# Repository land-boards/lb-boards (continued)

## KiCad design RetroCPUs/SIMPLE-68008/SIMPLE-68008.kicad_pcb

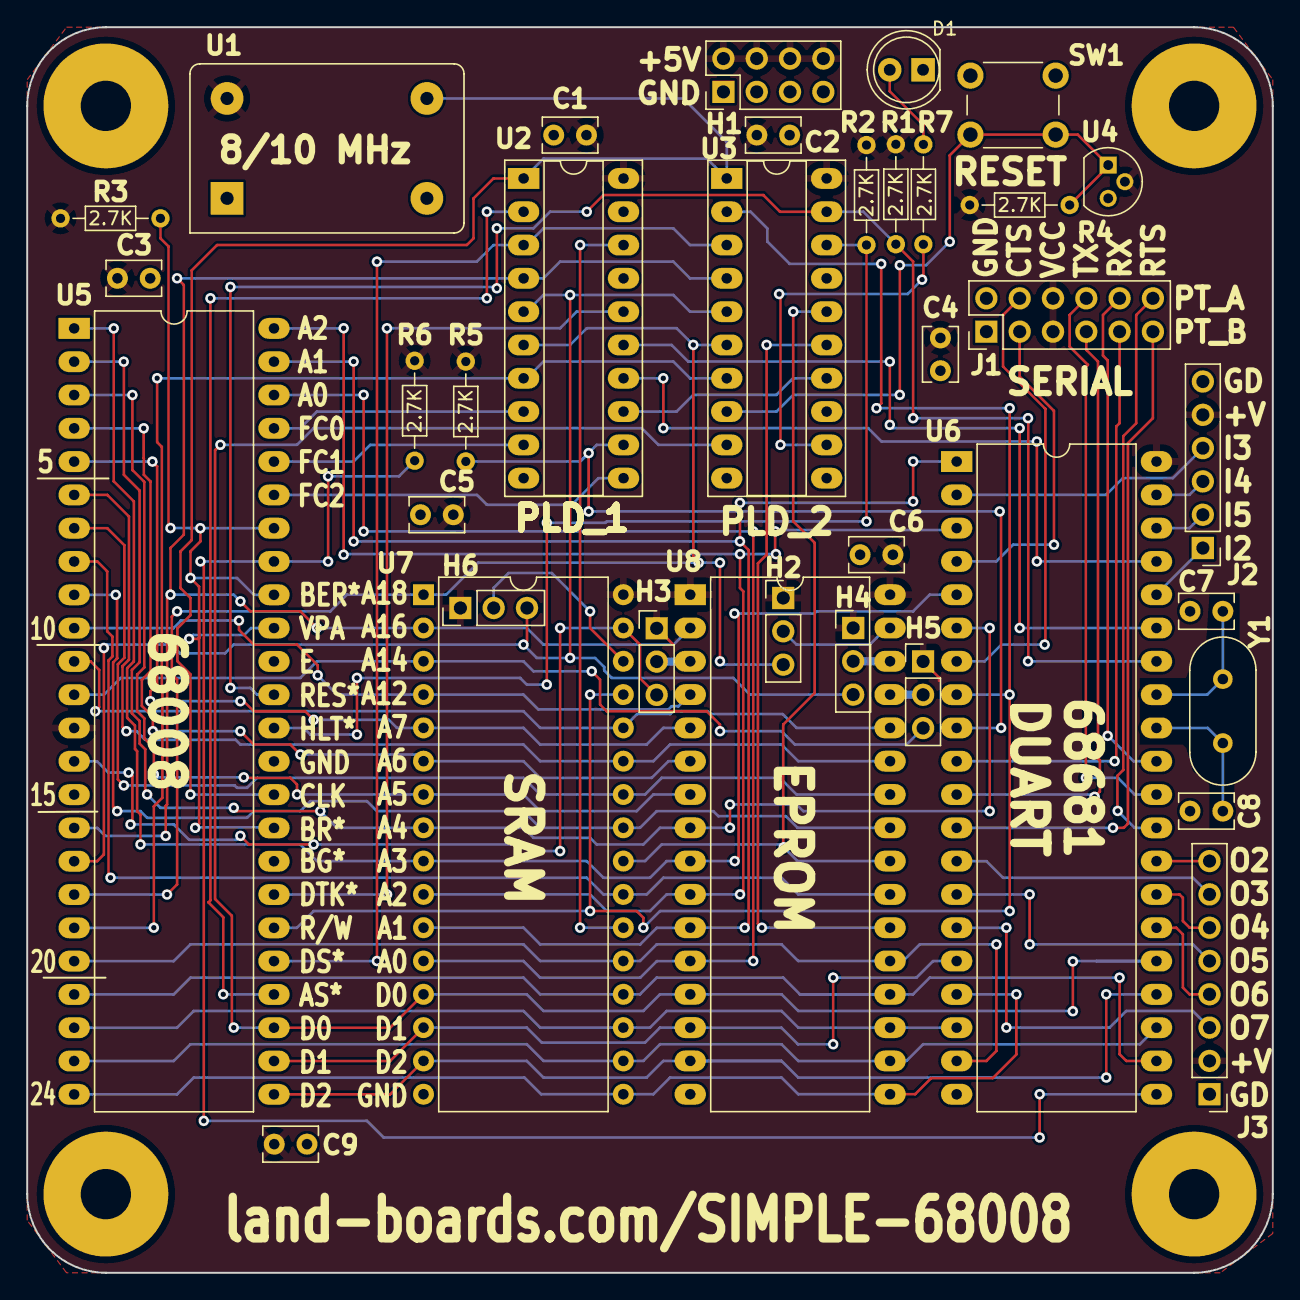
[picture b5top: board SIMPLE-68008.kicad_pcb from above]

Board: 2 copper layers, 95.0 x 95.0 mm, 41 parts (0 on the bottom side), 77 nets.

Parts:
C1, C2, C3, C4, C5, C6, C9: 0.1uF; C_Rect_L4.0mm_W2.5mm_P2.50mm
C7: 0-5pf; C_Rect_L4.0mm_W2.5mm_P2.50mm
C8: 10-15pF; C_Rect_L4.0mm_W2.5mm_P2.50mm
D1: LED_Filled; LED_D5.0mm
H1: HEADER, STRT, 2X4; PinHeader_2x04_P2.54mm_Vertical
H2, H3, H4, H5, H6: JUMPER (1X3); PinHeader_1x03_P2.54mm_Vertical
J1: Conn_02x06_Odd_Even; PinHeader_2x06_P2.54mm_Vertical
J2: Conn_01x06; PinHeader_1x06_P2.54mm_Vertical
J3: Conn_01x08; PinHeader_1x08_P2.54mm_Vertical
MTG1, MTG2, MTG3, MTG4: MTG_HOLE; MTG-6-32
R1, R2, R3, R4, R5, R6, R7: 2.7K; R_Axial_DIN0204_L3.6mm_D1.6mm_P7.62mm_Horizontal
SW1: PUSHBUTTON, 6MM; SW_PUSH_6mm_H8.5mm
TEST: COUPON; TEST_BLK-REAR
U1: 10 MHz; Oscillator_DIP-14_LargePads
U2, U3: GAL16V8; DIP-20_W7.62mm_Socket_LongPads
U4: DS1813-5 (OPT); TO-92
U5: MC68008D-10; DIP-48_W15.24mm_LongPads
U6: 68681; DIP-40_W15.24mm_LongPads
U7: AS6C4008-55PCN; DIP-32_W15.24mm
U8: 27C040; DIP-32_W15.24mm_LongPads
Y1: 3.6864 MHz; Crystal_HC49-U_Vertical

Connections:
/CPUA0: U5.46 (A0), U7.12 (A0), U8.12 (A0)
/CPUA1: U5.47 (A1), U6.1 (RS1), U7.11 (A1), U8.11 (A1)
/CPUA2: U5.48 (A2), U6.3 (RS2), U7.10 (A2), U8.10 (A2)
/CPUA3: U5.1 (A3), U6.5 (RS3), U7.9 (A3), U8.9 (A3)
/CPUA4: U5.2 (A4), U6.6 (RS4), U7.8 (A4), U8.8 (A4)
/CPUA5: U5.3 (A5), U7.7 (A5), U8.7 (A5)
/CPUA6: U5.4 (A6), U7.6 (A6), U8.6 (A6)
/CPUA7: U5.5 (A7), U7.5 (A7), U8.5 (A7)
/CPUA8: U5.6 (A8), U7.27 (A8), U8.27 (A8)
/CPUA9: U5.7 (A9), U7.26 (A9), U8.26 (A9)
/CPUA10: U5.8 (A10), U7.23 (A10), U8.23 (A10)
/CPUA11: U5.9 (A11), U7.25 (A11), U8.25 (A11)
/CPUA12: U5.10 (A12), U7.4 (A12), U8.4 (A12)
/CPUA13: U5.11 (A13), U7.28 (A13), U8.28 (A13)
/CPUA14: H5.3, U5.12 (A14), U7.3 (A14)
/CPUA15: H3.3, U5.14 (A15), U7.31 (A15)
/CPUA16: U2.4 (I4), U3.4 (I4), U5.16 (A16), U7.2 (A16), U8.2 (A16)
/CPUA17: H4.3, H6.3, U2.5 (I5), U3.5 (I5), U5.17 (A17)
/CPUA18: H2.3, U2.6 (I6), U3.6 (I6), U5.18 (A18), U7.1 (A18)
/CPUA19: U2.7 (I7), U3.7 (I7), U5.19 (A19)
/CPUAS*: U2.2 (I2), U5.28 (AS)
/CPUCLK: U1.8 (OUT), U2.1 (I1/CLK), U3.1 (I1/CLK), U5.34 (CLK)
/CPUD0: U3.9 (I9), U5.27 (D0), U6.25 (D0), U7.13 (DQ0), U8.13 (D0)
/CPUD1: U5.26 (D1), U6.16 (D1), U7.14 (DQ1), U8.14 (D1)
/CPUD2: U5.25 (D2), U6.24 (D2), U7.15 (DQ2), U8.15 (D2)
/CPUD3: U5.24 (D3), U6.17 (D3), U7.17 (DQ3), U8.17 (D3)
/CPUD4: U5.23 (D4), U6.23 (D4), U7.18 (DQ4), U8.18 (D4)
/CPUD5: U5.22 (D5), U6.18 (D5), U7.19 (DQ5), U8.19 (D5)
/CPUD6: U5.21 (D6), U6.22 (D6), U7.20 (DQ6), U8.20 (D6)
/CPUD7: U5.20 (D7), U6.19 (D7), U7.21 (DQ7), U8.21 (D7)
/CPUDS*: U2.3 (I3), U3.3 (I3), U5.29 (DS)
/CPUHLT*: R2.2, U3.18 (IO2), U5.36 (HALT)
/CPUIACK*: U2.14 (IO6), U6.37 (~IACK)
/CPURES*: R1.2, U3.19 (IO1), U5.37 (RESET), U6.34 (~RESET)
/CPUWR*: U3.2 (I2), U5.30 (R/W), U6.8 (R/~W), U7.29 (WE#)
/CTSA*: J1.4, U6.7 (IP0)
/CTSB*: J1.3, U6.4 (IP1)
/DDTACK*: R5.2, U2.12 (IO8), U6.9 (~DTACK)
/DTACK*: U2.16 (IO4), U5.31 (DTACK)
/DUARTCS*: U2.15 (IO5), U6.35 (~CS)
/EE_PIN3: H3.2, U8.3 (A15)
/EE_PIN29: H5.2, U8.29 (A14)
/EE_PIN30: H4.2, U8.30 (A17)
/EE_PIN31: H2.2, U8.31 (A18)
/FC0: U2.8 (I8), U5.45 (FC0)
/FC1: U2.9 (I9), U5.44 (FC1)
/FC2: U2.11 (I10/~OE), U5.43 (FC2)
/IP2: J2.1, U6.36 (IP2)
/IP3: J2.4, U6.2 (IP3)
/IP4: J2.3, U6.39 (IP4)
/IP5: J2.2, U6.38 (IP5)
/IRQ*: R6.2, U5.41 (IPL1), U6.21 (~IRQ)
/MEMRD*: U3.16 (IO4), U7.24 (OE#), U8.24 (~OE)
/OP2: J3.8, U6.28 (OP2)
/OP3: J3.7, U6.13 (OP3)
/OP4: J3.6, U6.27 (OP4)
/OP5: J3.5, U6.14 (OP5)
/OP6: J3.4, U6.26 (OP6)
/OP7: J3.3, U6.15 (OP7)
/POR*: R4.2, SW1.2, U3.8 (I8), U4.1
/PUP1: R3.2, U5.33 (BR), U5.39 (VPA), U5.40 (BERR), U5.42 (IPL0/2)
/RAMCS*: U2.18 (IO2), U7.22 (CE#)
/ROMCS*: U3.15 (IO5), U8.22 (~CE)
/RTSA*: J1.12, U6.29 (OP0)
/RTSB*: J1.11, U6.12 (OP1)
/RXA: J1.10, U6.31 (RXDA)
/RXB: J1.9, U6.10 (RXDB)
/SR_PIN30: H6.2, U7.30 (A17)
/SWAP: U2.13 (IO7), U3.14 (IO6)
/TXA: J1.8, U6.30 (TXDA)
/TXB: J1.7, U6.11 (TXDB)
GND: C1.1, C2.1, C3.1, C4.1, C5.1, C6.1, C7.2, C8.2, C9.1, D1.1 (K), H1.1, H1.3, H1.5, H1.7, J1.1, J1.2, J2.6, J3.1, SW1.1, U1.7 (GND), U2.10 (GND), U3.10 (GND), U4.3, U5.15 (GND), U5.35 (GND), U6.20 (GND), U7.16 (VSS), U8.16 (GND)
unnamed: D1.2 (A), R7.2
unnamed: R7.1, U3.12 (IO8)
unnamed: C8.1, U6.32 (X1/CLK), Y1.2
unnamed: C7.1, U6.33 (X2), Y1.1
VCC: C1.2, C2.2, C3.2, C4.2, C5.2, C6.2, C9.2, H1.2, H1.4, H1.6, H1.8, H2.1, H3.1, H4.1, H5.1, H6.1, J1.5, J1.6, J2.5, J3.2, R1.1, R2.1, R3.1, R4.1, R5.1, R6.1, U1.14 (VCC), U2.20 (VCC), U3.20 (VCC), U4.2, U5.13 (VCC), U6.40 (VCC), U7.32 (VCC), U8.1 (VPP), U8.32 (VCC)

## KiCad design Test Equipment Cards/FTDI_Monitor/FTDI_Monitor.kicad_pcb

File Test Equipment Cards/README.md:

lb-boards Test Equipment Cards Designs
======================================

land-boards.com - Test Equipment Cards Printed Circuit Board Designs
--------------------------------------------------------------------

Design files are kept here. Most are [Kicad based designs][Kicad].
[Kicad]: http://www.kicad-pcb.org/display/KICAD/KiCad+EDA+Software+Suite/ "Kicad is an open source electronic design suite which includes professional quality schematic capture and board layout tools."

See [our PCB Designs Website][ourWebsite] and our [land-boards Wiki][ourWiki].
[ourWebsite]: http://land-boards.com/content/ "land-boards.com website"
[ourWiki]: http://land-boards.com/blwiki/ "land-boards.com wiki"

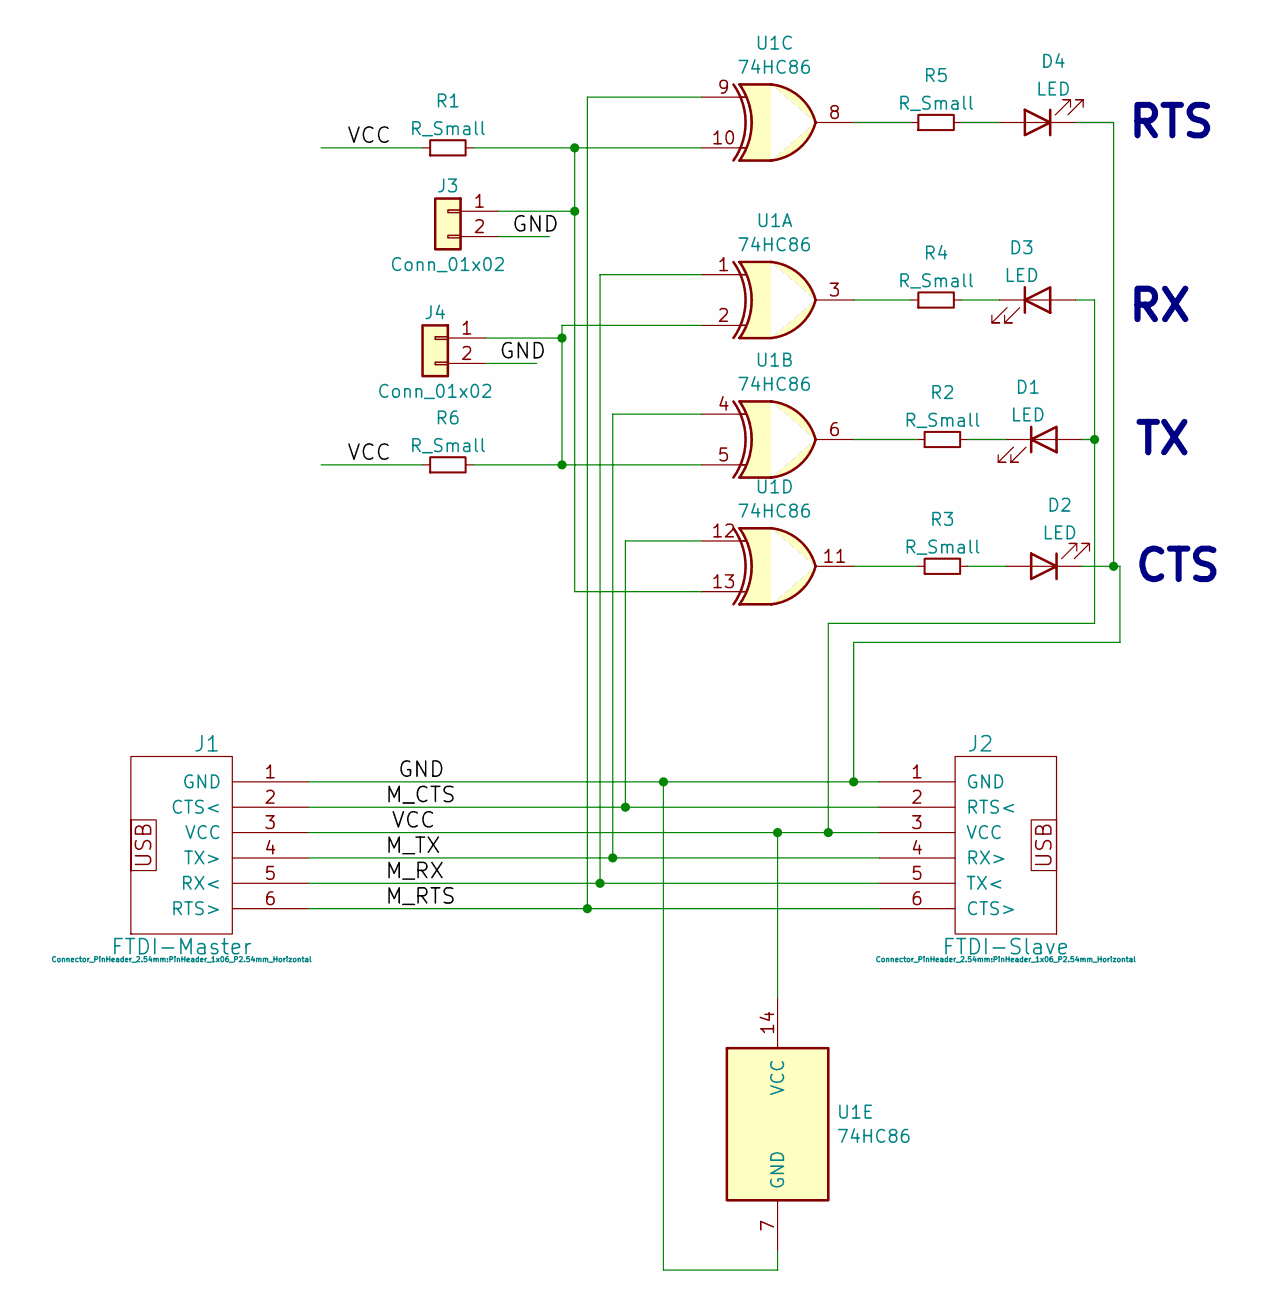
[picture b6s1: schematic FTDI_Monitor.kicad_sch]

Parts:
D1, D2, D3, D4: LED; LED_D5.0mm
J1: FTDI-Master; PinHeader_1x06_P2.54mm_Horizontal
J2: FTDI-Slave; PinHeader_1x06_P2.54mm_Horizontal
J3, J4: Conn_01x02; PinHeader_1x02_P2.54mm_Vertical
R1, R2, R3, R4, R5, R6: R_Small; R_Axial_DIN0204_L3.6mm_D1.6mm_P7.62mm_Horizontal
U1: 74HC86; DIP-14_W7.62mm_LongPads

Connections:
/GND: D2.1 (K), D4.1 (K), J1.1 (GND), J2.1 (GND), J3.2, J4.2, U1.7 (GND)
/M_CTS: J1.2 (CTS<), J2.2 (RTS<), U1.12
/M_RTS: J1.6 (RTS>), J2.6 (CTS>), U1.9
/M_RX: J1.5 (RX<), J2.5 (TX<), U1.1
/M_TX: J1.4 (TX>), J2.4 (RX>), U1.4
/VCC: D1.2 (A), D3.2 (A), J1.3 (VCC), J2.3 (VCC), R1.1, R6.1, U1.14 (VCC)
unnamed: D4.2 (A), R5.2
unnamed: D3.1 (K), R4.2
unnamed: D1.1 (K), R2.2
unnamed: D2.2 (A), R3.2
unnamed: J3.1, R1.2, U1.10, U1.13
unnamed: J4.1, R6.2, U1.2, U1.5
unnamed: R2.1, U1.6
unnamed: R3.1, U1.11
unnamed: R4.1, U1.3
unnamed: R5.1, U1.8

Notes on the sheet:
CTS
RTS

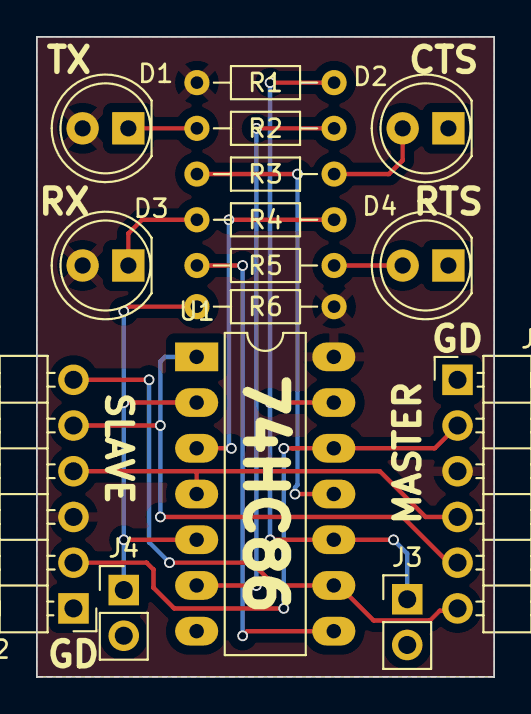
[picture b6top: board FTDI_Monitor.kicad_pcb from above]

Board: 2 copper layers, 25.4 x 35.6 mm, 15 parts (0 on the bottom side), 16 nets.

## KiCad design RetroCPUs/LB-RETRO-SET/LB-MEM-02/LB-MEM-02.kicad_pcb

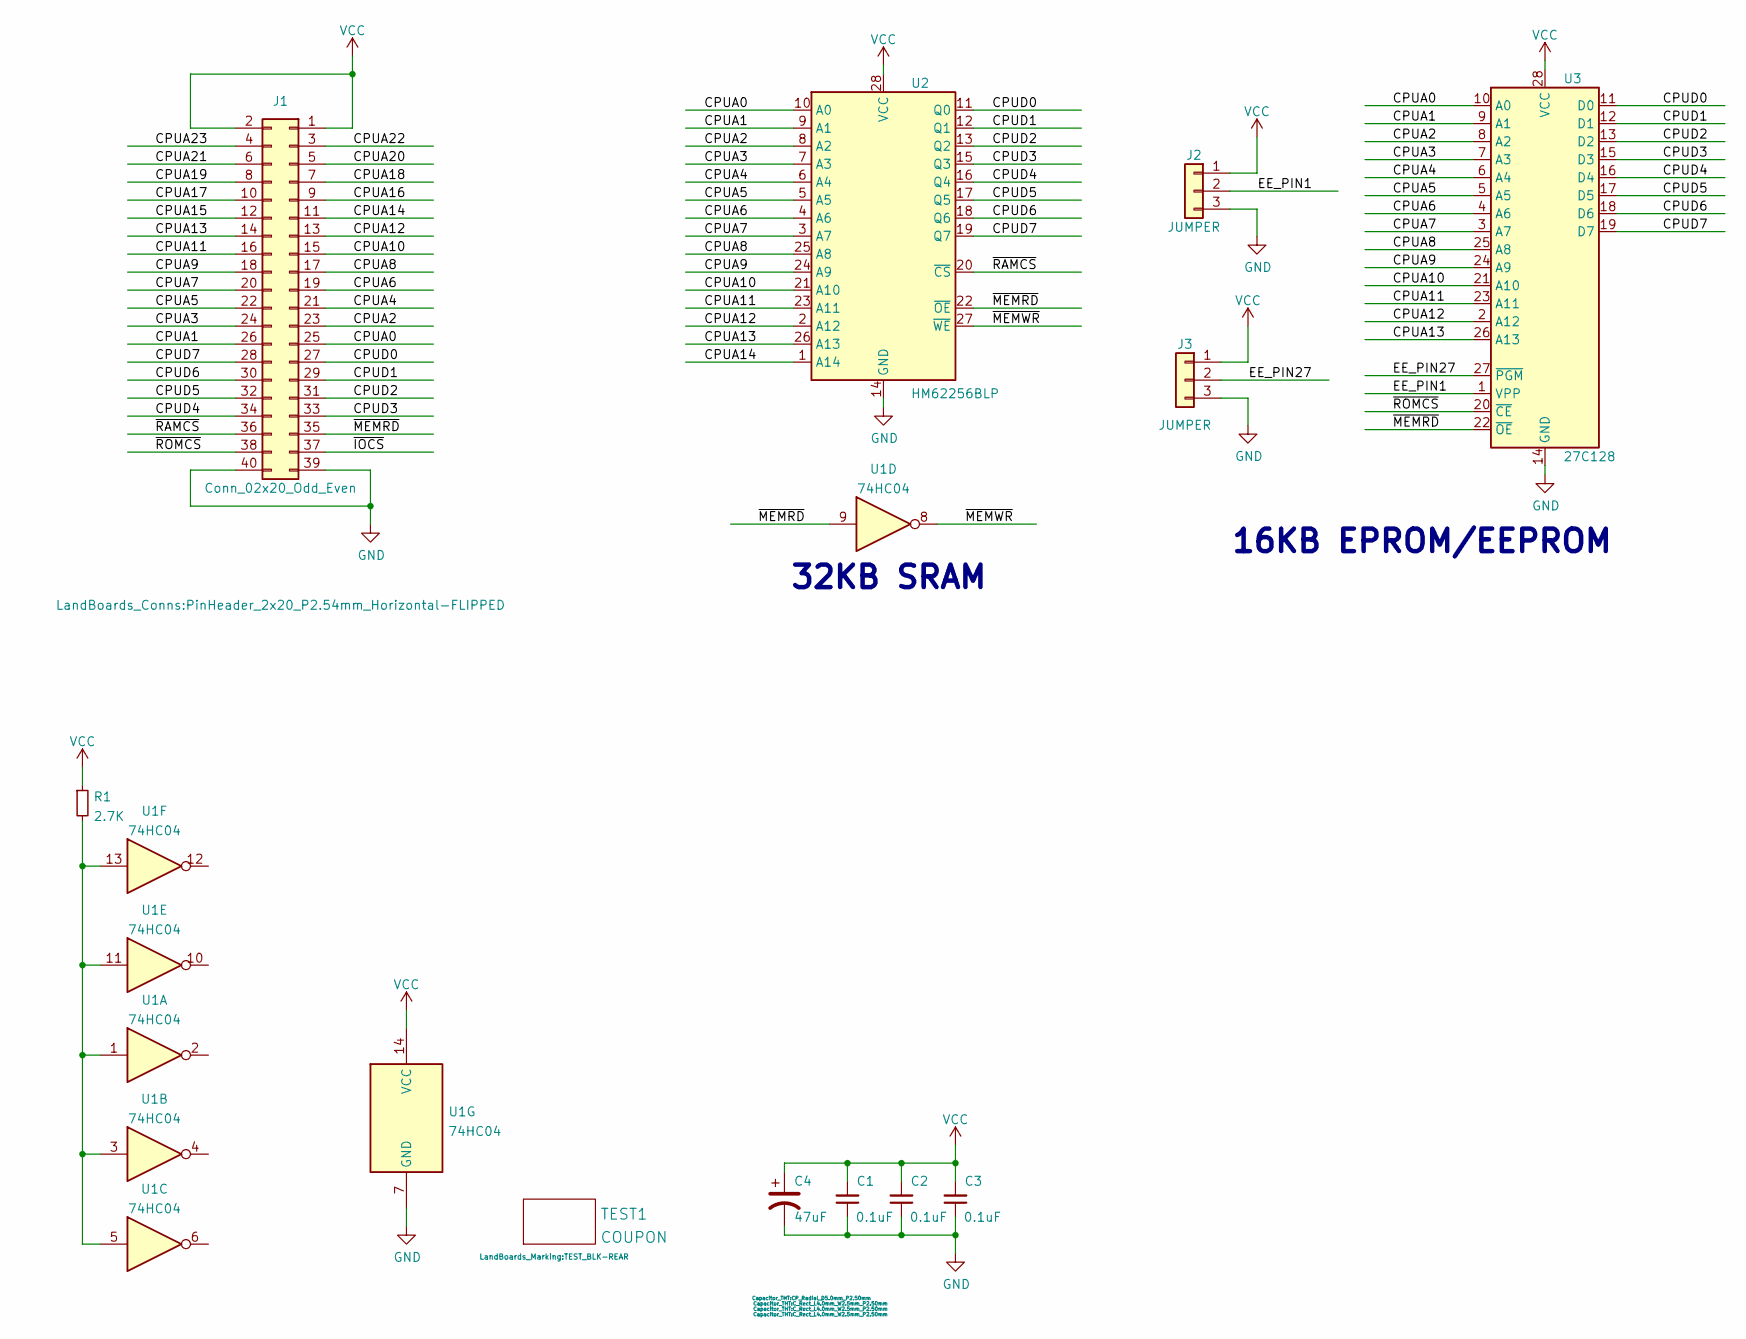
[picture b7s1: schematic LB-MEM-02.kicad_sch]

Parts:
C1, C2, C3: 0.1uF; C_Rect_L4.0mm_W2.5mm_P2.50mm
C4: 47uF; CP_Radial_D5.0mm_P2.50mm
J1: Conn_02x20_Odd_Even; PinHeader_2x20_P2.54mm_Horizontal-FLIPPED
J2, J3: JUMPER; PinHeader_1x03_P2.54mm_Vertical
R1: 2.7K; R_Axial_DIN0204_L3.6mm_D1.6mm_P7.62mm_Horizontal
TEST1: COUPON; TEST_BLK-REAR
U1: 74HC04; DIP-14_W7.62mm_LongPads
U2: HM62256BLP; DIP-28_W15.24mm_LongPads
U3: 27C128; DIP-28_W15.24mm_LongPads

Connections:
/CPUA0: J1.25, U2.10 (A0), U3.10 (A0)
/CPUA1: J1.26, U2.9 (A1), U3.9 (A1)
/CPUA2: J1.23, U2.8 (A2), U3.8 (A2)
/CPUA3: J1.24, U2.7 (A3), U3.7 (A3)
/CPUA4: J1.21, U2.6 (A4), U3.6 (A4)
/CPUA5: J1.22, U2.5 (A5), U3.5 (A5)
/CPUA6: J1.19, U2.4 (A6), U3.4 (A6)
/CPUA7: J1.20, U2.3 (A7), U3.3 (A7)
/CPUA8: J1.17, U2.25 (A8), U3.25 (A8)
/CPUA9: J1.18, U2.24 (A9), U3.24 (A9)
/CPUA10: J1.15, U2.21 (A10), U3.21 (A10)
/CPUA11: J1.16, U2.23 (A11), U3.23 (A11)
/CPUA12: J1.13, U2.2 (A12), U3.2 (A12)
/CPUA13: J1.14, U2.26 (A13), U3.26 (A13)
/CPUA14: J1.11, U2.1 (A14)
/CPUA15: J1.12
/CPUA16: J1.9
/CPUA17: J1.10
/CPUA18: J1.7
/CPUA19: J1.8
/CPUA20: J1.5
/CPUA21: J1.6
/CPUA22: J1.3
/CPUA23: J1.4
/CPUD0: J1.27, U2.11 (Q0), U3.11 (D0)
/CPUD1: J1.29, U2.12 (Q1), U3.12 (D1)
/CPUD2: J1.31, U2.13 (Q2), U3.13 (D2)
/CPUD3: J1.33, U2.15 (Q3), U3.15 (D3)
/CPUD4: J1.34, U2.16 (Q4), U3.16 (D4)
/CPUD5: J1.32, U2.17 (Q5), U3.17 (D5)
/CPUD6: J1.30, U2.18 (Q6), U3.18 (D6)
/CPUD7: J1.28, U2.19 (Q7), U3.19 (D7)
/EE_PIN1: J2.2, U3.1 (VPP)
/EE_PIN27: J3.2, U3.27 (~PGM)
/~IOCS: J1.37
/~MEMRD: J1.35, U1.9, U2.22 (~OE), U3.22 (~OE)
/~MEMWR: U1.8, U2.27 (~WE)
/~RAMCS: J1.36, U2.20 (~CS)
/~ROMCS: J1.38, U3.20 (~CE)
GND: C1.1, C2.1, C3.1, C4.2, J1.39, J1.40, J2.3, J3.3, U1.7 (GND), U2.14 (GND), U3.14 (GND)
unnamed: R1.2, U1.1, U1.3, U1.5, U1.11, U1.13
VCC: C1.2, C2.2, C3.2, C4.1, J1.1, J1.2, J2.1, J3.1, R1.1, U1.14 (VCC), U2.28 (VCC), U3.28 (VCC)

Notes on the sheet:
32KB SRAM
16KB EPROM/EEPROM

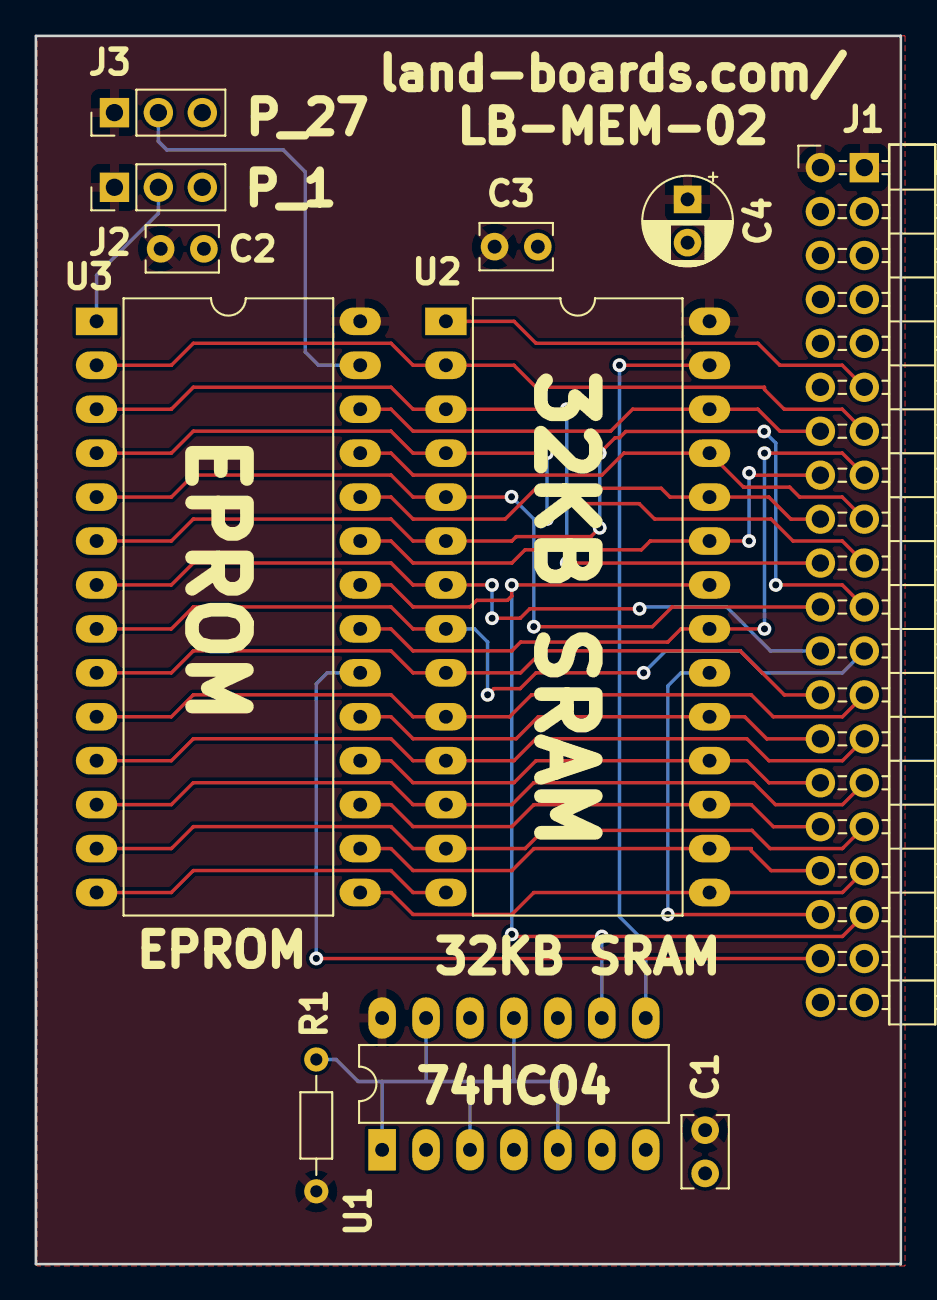
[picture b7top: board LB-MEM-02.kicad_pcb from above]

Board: 2 copper layers, 50.0 x 71.0 mm, 12 parts (0 on the bottom side), 32 nets.

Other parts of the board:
TEST: COUPON; TEST_BLK-REAR

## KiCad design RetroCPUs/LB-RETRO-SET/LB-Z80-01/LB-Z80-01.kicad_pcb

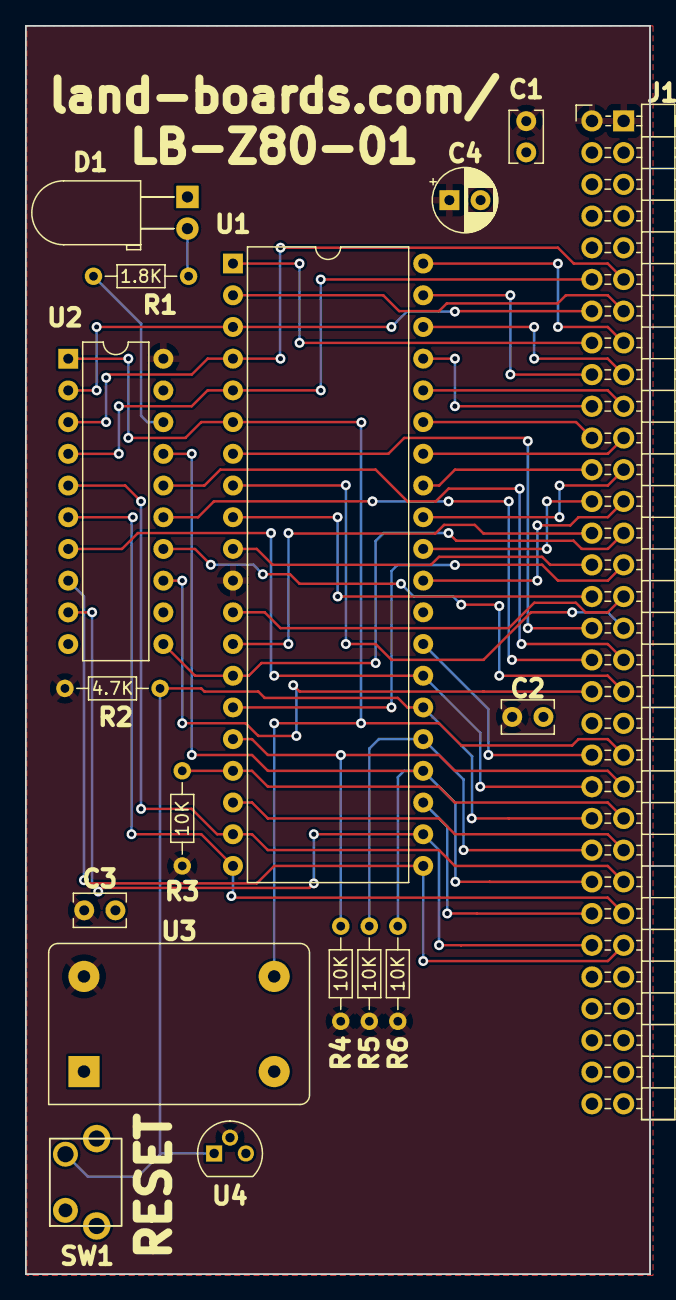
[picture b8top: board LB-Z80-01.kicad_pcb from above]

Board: 2 copper layers, 50.0 x 100.0 mm, 18 parts (0 on the bottom side), 46 nets.

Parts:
C1, C2, C3: 0.1uF; C_Rect_L4.0mm_W2.5mm_P2.50mm
C4: 47uF; CP_Radial_D5.0mm_P2.50mm
D1: LED_Small; LED_D5.0mm_Horizontal_O3.81mm_Z9.0mm
J1: Conn_02x32_Odd_Even; PinHeader_2x32_P2.54mm_Horizontal-FLIPPED
R1: 1.8K; R_Axial_DIN0204_L3.6mm_D1.6mm_P7.62mm_Horizontal
R2: 4.7K; R_Axial_DIN0204_L3.6mm_D1.6mm_P7.62mm_Horizontal
R3, R4, R5, R6: 10K; R_Axial_DIN0204_L3.6mm_D1.6mm_P7.62mm_Horizontal
SW1: SW_Push; SW_PUSH_VERT
TEST1: COUPON; TEST_BLK-REAR
U1: Z80CPU; DIP-40_W15.24mm
U2: GAL16V8; DIP-20_W7.62mm
U3: OSC; Oscillator_DIP-14_LargePads
U4: DS1813-5; TO-92

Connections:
/CPUA0: J1.25, U1.30 (A0)
/CPUA1: J1.26, U1.31 (A1)
/CPUA2: J1.23, U1.32 (A2)
/CPUA3: J1.24, U1.33 (A3)
/CPUA4: J1.21, U1.34 (A4)
/CPUA5: J1.22, U1.35 (A5)
/CPUA6: J1.19, U1.36 (A6)
/CPUA7: J1.20, U1.37 (A7)
/CPUA8: J1.17, U1.38 (A8)
/CPUA9: J1.18, U1.39 (A9)
/CPUA10: J1.15, U1.40 (A10)
/CPUA11: J1.16, U1.1 (A11)
/CPUA12: J1.13, U1.2 (A12)
/CPUA13: J1.14, U1.3 (A13), U2.2 (I2)
/CPUA14: J1.11, U1.4 (A14), U2.3 (I3)
/CPUA15: J1.12, U1.5 (A15), U2.4 (I4)
/CPUCLK: J1.41, U1.6 (~CLK), U2.1 (I1/CLK), U3.8 (OUT)
/CPUD0: J1.27, U1.14 (D0), U2.11 (I10/~OE)
/CPUD1: J1.29, U1.15 (D1)
/CPUD2: J1.31, U1.12 (D2)
/CPUD3: J1.33, U1.8 (D3)
/CPUD4: J1.34, U1.7 (D4)
/CPUD5: J1.32, U1.9 (D5)
/CPUD6: J1.30, U1.10 (D6)
/CPUD7: J1.28, U1.13 (D7)
/LED: R1.2, U2.18 (IO2)
/RFSH: J1.42, U1.28 (~RFSH)
/~BUSACK: J1.52, U1.23 (~BUSACK)
/~BUSRQ: J1.48, R5.2, U1.25 (~BUSRQ)
/~CPURD: J1.53, U1.21 (~RD), U2.8 (I8)
/~CPURST: J1.46, R2.2, SW1.2, U1.26 (~RESET), U4.1
/~CPUWR: J1.54, U1.22 (~WR), U2.9 (I9)
/~HALT: J1.47, U1.18 (~HALT)
/~INT: J1.43, R4.2, U1.16 (~INT)
/~IOCS: J1.37, U2.14 (IO6)
/~IORQ: J1.51, U1.20 (~IORQ), U2.6 (I6)
/~M1: J1.44, U1.27 (~M1), U2.7 (I7)
/~MEMRD: J1.35, U2.16 (IO4)
/~MREQ: J1.49, U1.19 (~MREQ), U2.5 (I5)
/~NMI: J1.45, R3.2, U1.17 (~NMI)
/~RAMCS: J1.36, U2.15 (IO5)
/~ROMCS: J1.38, U2.13 (IO7)
/~WAIT: J1.50, R6.2, U1.24 (~WAIT), U2.17 (I03)
GND: C1.1, C2.1, C3.1, C4.2, D1.1 (K), J1.39, J1.40, SW1.1, U1.29 (GND), U2.10 (GND), U3.7 (GND), U4.3
unnamed: D1.2 (A), R1.1
VCC: C1.2, C2.2, C3.2, C4.1, J1.1, J1.2, R2.1, R3.1, R4.1, R5.1, R6.1, U1.11 (VCC), U2.20 (VCC), U3.14 (VCC), U4.2

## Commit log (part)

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2022-06-01 QT Py
2022-06-01 QT Py stuff
2022-06-01 Working QT Py code
2022-06-04 QT Py and others
2022-06-06 MyMenu
2022-06-09 KiCad Temptates and cards
2022-06-09 ZIP templates
2022-06-09 KiCad templates
2022-06-10 QTPy
2022-06-13 MAX7219 card
2022-06-14 QTPy49 pics
2022-06-15 Pics of QTPy49
2022-06-16 SD Loader
2022-06-17 card pics
2022-06-18 PiPicoMite03
2022-06-18 PiPicoMite03 design
2022-06-19 Card docs
2022-06-19 I2CIO16-DB25 svhematic
2022-06-19 I2C-SERIAL Card
2022-06-20 More pics
2022-06-20 More card docs
2022-06-22 Card updates
2022-06-24 LED cards
2022-06-25 GPS Std
2022-06-26 Shuffle around pictures
2022-06-26 pics
2022-06-28 GPS Freq Std V2
2022-06-28 Cost est
2022-07-02 Ordered PCBs
2022-07-03 RTC pics
2022-07-04 PulseGen pics
2022-07-08 DRIVE50 card
2022-07-08 MyMenu_Rev5
2022-07-08 add pics
2022-07-09 Panel Cutouts
2022-07-09 fix name
2022-07-10 VFO-003
2022-07-17 PiPicoMite stuff
2022-07-18 PicoVGA build
2022-07-20 QTPy apps
2022-07-21 specs
2022-07-24 QTPy49-01 design
2022-07-26 OpAmp4
2022-07-29 New cards
2022-07-29 Op Amp 4 docs
2022-07-31 GPS and DRIVE50 cards
2022-07-31 MAX7219X4 docs
2022-08-01 Card docs / pics
2022-08-02 New cards order
2022-08-03 PicoVGA pics
2022-08-03 Crop pics
2022-08-04 MAX7219X4 pics/docs
2022-08-04 PicoVGA
2022-08-11 RETRO-65C816 conns
2022-08-13 QTPy49-01 pics
2022-08-15 SD Loader on QTPy49-01
2022-08-15 TinyPS2 working
2022-08-17 UNI-OPAMP-04
2022-08-19 QTPy49-01 card
2022-08-20 Level Shifter card
2022-08-25 opamp
2022-08-27 update ITX design files
2022-08-30 ITX cards
2022-08-30 New pics renamed
2022-08-30 More FGPA-ITX-01 card tweeks
2022-08-30 ITX-BKOUT card
2022-08-31 ITX card files - ordered
2022-09-03 ESP32-VGA
2022-09-03 ESP32-VGA files
2022-09-04 PSOC5 card
2022-09-05 ODAS-PSOC5 card
2022-09-07 XARDS UPDATES
2022-09-10 BUILDS OF GRANT SEARLE SIMPLE CPUS ON A BACKPLANR
2022-09-12 SIMPLE CPU DESIGNS
2022-09-12 MC68B02 CPU
2022-09-14 68008 CARD
2022-09-15 68008 CPU card
2022-09-15 SIMPLE-68008
2022-09-15 SIMPLE-68008 AND SCREWDUINO
2022-09-15 SHUFFLE FTDI PINS
2022-09-18 board updates
2022-09-18 FPGA-ITX-01 UPDATES FROM BUILD
2022-09-20 IFPGA-ITX PICS
2022-09-23 Synth boards
2022-09-24 SYNTH DESIGNS
2022-09-25 AUDIO CARDS
2022-09-29 SYNTHS
2022-10-04 SYNTH and RPPSOC
2022-10-04 SHUFFLE FOLDERS
2022-10-04 p/s, vco1
2022-10-06 Boards details
2022-10-07 synth pieces
2022-10-10 VCO-01 REWORK
2022-10-11 CONTROL
2022-10-11 synth parts
2022-10-13 SYNTH Card stuff
2022-10-17 MORE CARD STUFF
2022-10-18 MORE SYNTH
2022-10-18 RE-NAME FOLDER
2022-10-20 Getting ready to order PCBs
2022-11-06 ADSR working
2022-11-06 SCHEMATIC
2022-11-06 ADSR SCHEMATICS
2022-11-06 ADSR
2022-11-06 pics ADSR
2022-11-06 SHUFFLE PLUS ADD PICS
2022-11-07 NANO
2022-11-08 MOZZI CARD
2022-11-08 ER CARDS
2022-11-11 SYNTH CARDS
2022-11-12 SLEW RATE CARD
2022-11-13 Braids and other stuff
2022-11-13 Braids front panel
2022-11-14 Beaks and Braids
2022-11-14 Thru Hole Braids files
2022-11-15 more pics plus PDF of Wiki Page
2022-11-15 Orders
2022-11-15 NOISE SCHEMATIC
2022-11-15 noise gen
2022-11-25 cards
2022-11-28 Visible BOM plugin
2022-11-29 SYNTH updates
2022-12-06 Roland D-5 Manuals
2022-12-09 Eurorack sound modules
2022-12-23 Beaks built and working
2022-12-25 Braids files
2022-12-25 Manuals
2022-12-26 MUTABLE INSTRUMENTS STUFF
2022-12-26 TWIGA
2022-12-26 TWIGS
2022-12-27 STIX
2022-12-27 STIX - DiY MI Branches
2023-01-08 ER-SCOPE working
2023-01-08 ER-SCOPE
2023-01-10 ER-MIDI card
2023-01-16 Ordered cards
2023-01-18 ER-DELAY CARD
2023-01-19 ER-DRUMS
2023-01-23 ER-DELAY-01 DESIGN
2023-01-25 ER-VCF
2023-02-01 SAMPLE AND HOLD
2023-02-02 CARD DOC UPDATES
2023-02-11 pipicomite03 end panels
2023-02-12 ER-DELAY-02
2023-03-01 SIMPLE CPUs
2023-03-11 ER-VCF-02 working
2023-03-25 SIMPLE-6802 PICS PLUS FORTH
2023-03-26 SIMPLE-6802
2023-03-26 SIMPLE-6802 TINYBASIC
2023-03-26 TinyBASIC WORKING
2023-03-29 More modules
2023-03-30 optofast-2 card
2023-03-30 ODASFAST-2 TEST
2023-04-05 POW PICS
2023-04-06 GRIS
2023-04-26 Move to Kicad 7
2023-05-10 PCBs ordered
2023-05-29 FPGA-ITX
2023-06-02 GRIDS
2023-08-08 OptoIn8
2024-06-20 Lots of updates
2024-06-27 68K CPU and others
2024-07-05 Pics of DRIVE50 card
2024-08-29 LB cards
2024-09-07 LB-RETRO card set updates
2024-09-10 LB-RETRO-SET
2024-09-10 Update 6809 CPU
2024-09-13 Card updates - Add LEDs to CPU cards
2024-09-20 LB-RETRO CPUs UPDATES
2024-09-23 CARD FILES
2024-10-03 Card stuff
2024-10-09 Ordered PCBa
2024-10-11 Compact Flash
2024-10-14 Z80 PICS
2024-10-16 CARD CHECKOUTS
2024-12-02 Retro backplane computer pics
